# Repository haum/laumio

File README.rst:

Laumio
######

Setup
=====

You need the Arduino IDE.

Install ESP8266 toolkit for Arduino
-----------------------------------

Instructions here : https://github.com/esp8266/Arduino

Install libraries
-----------------

- https://github.com/adafruit/Adafruit_NeoPixel
- https://github.com/bblanchon/ArduinoJson

Compiling
=========

Open sketch using Arduino
-------------------------

Open the laumio.ino sketch.

Select board
------------

Select the board in the board type to "WeMos D1 R2 & mini".

Flash
-----

You can now compile and flash the sketch to the board.

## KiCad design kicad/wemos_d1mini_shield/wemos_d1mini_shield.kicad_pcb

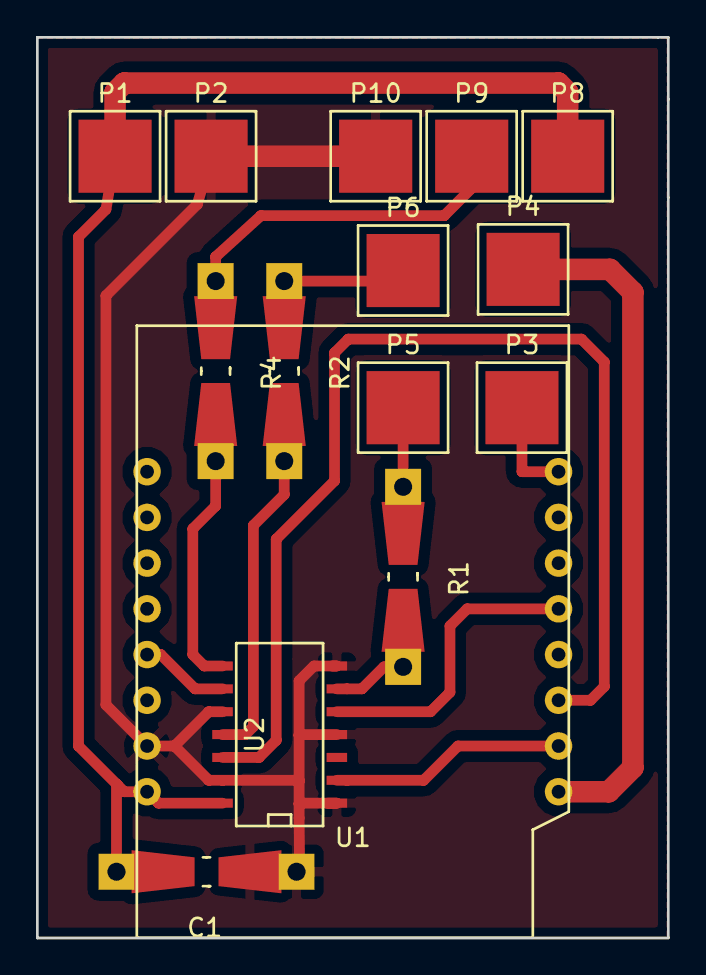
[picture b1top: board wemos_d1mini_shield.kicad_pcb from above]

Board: 2 copper layers, 35.1 x 50.0 mm, 15 parts (0 on the bottom side), 14 nets.

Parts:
C1: C; Resistor_SMD+THTuniversal_0805to1206_RM10_HandSoldering
P1, P2, P3, P4, P5, P6, P8, P9, P10: 1Pin
R1, R2, R4: R; Resistor_SMD+THTuniversal_0805to1206_RM10_HandSoldering
U1: WeMosD1Mini
U2: 74LS125; SOIC-14_N

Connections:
GND: C1.1, P2.1, P10.1, U1.7, U2.1, U2.4, U2.7, U2.10, U2.13
unnamed: P3.1, U1.16
unnamed: P4.1, U1.9
unnamed: P5.1, R1.1
unnamed: P6.1, R2.1
unnamed: P9.1, R4.1
unnamed: R1.2, U2.6
unnamed: R2.2, U2.11
unnamed: R4.2, U2.8
unnamed: U1.5, U2.9
unnamed: U1.10, U2.2
unnamed: U1.11, U2.12
unnamed: U1.13, U2.5
VCC: C1.2, P1.1, P8.1, U1.8, U2.14

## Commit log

2016-04-15 Import tiny code that support our hw setup (LEDs and MCU)
2016-04-15 Add Makefile for indent and mrproper commands
2016-04-15 Git: ignore some files
2016-04-15 Add Wi-Fi connect methods
2016-04-16 Wi-Fi: minor display enhancement
2016-04-16 Put LEDs related things into dedicated class
2016-04-16 Fix typo
2016-04-16 Add an HTTP server
2016-04-17 Implement minimal API to set led(s)
2016-04-17 Provides a python module with test to drive Laumio
2016-04-17 tests/ are not tests ;-)
2016-04-17 Examples: rename rgb.py to fill-rgb.py
2016-04-17 Examples: allow fill-rgb.py to run from anywhere
2016-04-19 LaumioLeds already check if LED index is valid
2016-04-19 LaumioApi: reply correctly according to status
2016-04-19 Python: add status feature
2016-04-19 Python module: rename fill() to fillColor()
2016-04-19 Shell: add status example
2016-04-19 Python module: add function to drive each pixel color
2016-04-19 Python module: fix Json response
2016-04-23 Rename fill() to fillColor()
2016-04-23 make indent
2016-04-23 Provide UDP remote control
2016-04-24 Import Fado mod from LHAUMpions repository
2016-04-24 Import CAM files based on CAD for Fado mod from LHAUMpions repository
2016-04-24 Import CAD files for Fado mod, reworked by Jblb
2016-04-24 Import CAM files for Fado mod, reworked by Jblb
2016-04-24 CAD: cleanup file and remove old layers
2016-04-24 MDNS: add mDNS capability
2016-04-24 CAD: try a new design with less parts
2016-04-25 CAD: ensure its possible to enter into sphere
2016-04-25 CAD: draw two main parts
2016-04-25 add CR/LF after serial init to separate info from startup grabage in serial terminal
2016-04-29 kicad: add wemosd1mini part
2016-04-29 kicad: add schematic for wemos_d1mini_shield
2016-04-29 kicad: associate components
2016-04-29 kicad: add WeMosD1Mini footprint
2016-04-29 kicad: add project (oups)
2016-04-29 kicad: add null routage
2016-04-29 kicad: simplify schematic and begin of routage (WIP)
2016-05-05 Use D3 on Wemos D1 mini
    This prevents from having the onboard blue led on (D4)
2016-05-05 Update PCB design
    This design is working and have been used for "BienVenus sur Venus".
2016-05-05 Add 8 Wemos D1 mini shield PCBs panelized 4x2
2016-05-05 Git: ignore *-bak
2016-06-09 Added README
2016-06-10 Benchmark with French flag
2016-06-10 Mememto for old hardware version
2016-06-11 Added clean target for Makefile
2016-06-11 Added LaumioConnect helper
2016-06-11 Added EEPROM.begin missing call
2016-06-11 Added LaumioAP helper
2016-06-11 Fix Netbeans comment
2016-06-18 Added Ring mapping, reworked UDP parsing
2016-06-18 Bashception for socat
2016-06-18 Fixed bad animation on start
2016-06-18 Fix from last session
2016-06-18 Fixed various bugs
2016-06-18 Using makefile
2016-06-18 Fixed indent rule in Makefile
2016-06-18 Indent
2016-06-18 Fixed make clean
2016-07-27 Add documentation v1
2016-07-27 correct Ring-wise control exemple
2016-07-27 Listen on /api and /api/
2016-07-27 Make sure HTTP responses are correct JSON objects and state the right hostname
2016-07-27 Use urllib to get Laumio's status
2016-07-27 Set send() to be private and do minimal error handling
2016-07-27 Add comments on each method and the class
2016-07-27 Add helper to wipe the Laumio
2016-07-27 Add the Ring primitive according to Laumio's firmware
2016-07-27 Exposing ColorWipe function via UDP
2016-07-27 Exposing AnimateRainbox function via UDP
2016-07-27 Add consistency to values
2016-07-27 Write IP address to serial when connected
2016-07-27 add port used for udp data
2016-07-27 Rename wipe function to wipeOut
2016-07-27 Expose the colorWipe UDP endpoint
2016-07-27 Expose the rainbow UDP endpoint
2016-07-27 Rephrase port indication and introduce the REST api
2016-07-27 Add animations doc on the Bare UDP side
2016-07-27 Informe on the non-completness of the JSON implementation
2016-07-27 Reflect in the documentation changes to the python library
2016-07-27 Now the animation engine is exposed through UDP
2016-07-27 Indicate the meaning of the color codes and animations at boot
2016-08-02 Column filling feature (full support in C++, API, bash, python and documentation)
2016-08-02 Example and corrections for column filling.
2016-08-03 Correcting documentation, improving shell example.
2016-08-06 add inclusions to compile with Arduino 1.6.5 version
2016-08-06 Add ability to send multiple commands in one UDP packet
2016-08-18 modification du script bash - ajout du paramètre -n sur la commande echo
2016-08-18 modification de la documentation
2016-08-26 Test with another neopixel lib
2016-08-30 Removing AP Mode in case of not found AP, delay and restart instead
2016-09-28 Add pupitre tools
2016-10-01 Improving bash interface documentation page.
2016-10-01 Correcting mitakes in doc
2016-10-01 Adding french version for documentation.
2016-10-02 Slight adddenda.
2016-10-02 Struggling with code-block for one line, trying pygments.
2016-10-14 Adding README for Laumio Desk.
2016-10-14 Correcting syntax error in Laumio Desk README.
2016-10-14 Thought the two errors were corrected...
2016-10-17 Things always come in threes
2017-01-26 ajout d'une représentation png du shield
2017-02-09 add schematic in pdf
2019-01-04 creation class MQTT (wip)
2019-01-05 Add basic structure for LaumioMQTT (untested)
2019-01-07 add OTA
2019-01-07 add MQTT connect function
2019-01-08 change EthernetClient to WiFiClient and debug in connect fonction / add debug in subscribe function
2019-01-08 more debug in subscribe function - get function name from topic
2019-01-08 subscribe to topics named after this laumio for individual control
2019-01-08 rework serial output of MQTT handler
2019-01-08 advertise presence on connection with name
2019-01-08 advertise also on discover command
2019-01-08 fix syntax error in previous commit
2019-01-08 rename LaumioApi to more suitable LaumioHttpApi
2019-01-08 add json command interpreter in LaumioLeds
2019-01-08 simplify LaumioHttpApi with json interpreter from leds
2019-01-08 add json commands to MQTT interface
2019-01-08 harmonize http api answer
2019-01-08 add some show calls in LaumioLeds::jsonCommands
2019-01-08 update doc a bit
2019-01-08 fix topic matching conditionals to stop comparison before the trailing command
2019-01-08 set the number of pixels to the correct number for standard laumios
2019-01-09 binaire du code laumio
2019-01-11 ajout d'un status de connection MQTT
2019-01-11 typo et armonisation des nomages
2019-01-13 improuve status repport topic
2019-01-19 add precision of delay unit in api doc
2019-01-19 fix MQTT binary commands
2019-01-21 nex binary firmware
2019-01-23 Transform multiple fields call to JSON in HttpAPI
2019-01-23 Add alternative way of describing colors in Json command
2019-01-23 Change home page
2019-01-24 Remove useless half-abstraction poorly implemented LaumioConnect
2019-01-24 Introduce LaumioConfig to host configuration
2019-01-24 Rename LaumioAP page name
2019-01-24 Replace *-config.h by LaumioConfig
2019-01-24 Bring web server to main file
2019-01-24 Add HttpConfig handler
2019-01-24 Add config in main page
2019-01-24 Fix arguments parsing since "plain" is not counted
2019-01-24 Add a bit of javascript in index page
2019-01-24 Apply clang-format on code
2019-01-24 Add reboot config-command
2019-01-24 Rename some vars in LaumioMQTT
2019-01-24 Rename some symbols in LaumioLeds
2019-01-24 Remove useless comments in LaumioHttpApi and LaumioHttpConfig
2019-01-24 Remove useless hello page in LaumioAP
2019-01-24 Isolate OTA logs in helper files
2019-01-24 Rework laumio.ino
2019-01-24 Reduce MQTT reconnect attempt rate and remove useless debug message
2019-01-24 Handle captured DNS in webserver
2019-01-24 Fix LaumioConfig::ConfigString<N>::setValue()
2020-03-09 change wifi password length to 64
2020-03-09 change need by upgrade ArduinoJSON library
2020-03-09 debug need by library update
2020-03-09 add MDNS.begin before MDNS.addService
2020-03-10 beter way to manage MDNS stuff
